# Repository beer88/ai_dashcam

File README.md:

# AI Dashcam System

An AI-powered Dashcam system built using Raspberry Pi that provides real-time video recording, intelligent event detection, and vehicle monitoring. The system integrates hardware and software components to enhance driving safety and provide smart surveillance capabilities.

## Features

- Real-time video recording using Raspberry Pi Camera
- AI-based object detection
- Automatic event recording
- GPS tracking support
- GSM/4G connectivity for remote monitoring
- Data storage on SD card
- Easy integration with vehicle systems

## Hardware Components

- Raspberry Pi 4
- Raspberry Pi Camera Module
- GPS Module
- GSM/4G Module
- Micro SD Card
- Power Supply Module
- Vehicle Mount

## Software Requirements

- Python 3
- OpenCV
- TensorFlow / PyTorch
- Raspberry Pi OS
- Git

## Project Structure

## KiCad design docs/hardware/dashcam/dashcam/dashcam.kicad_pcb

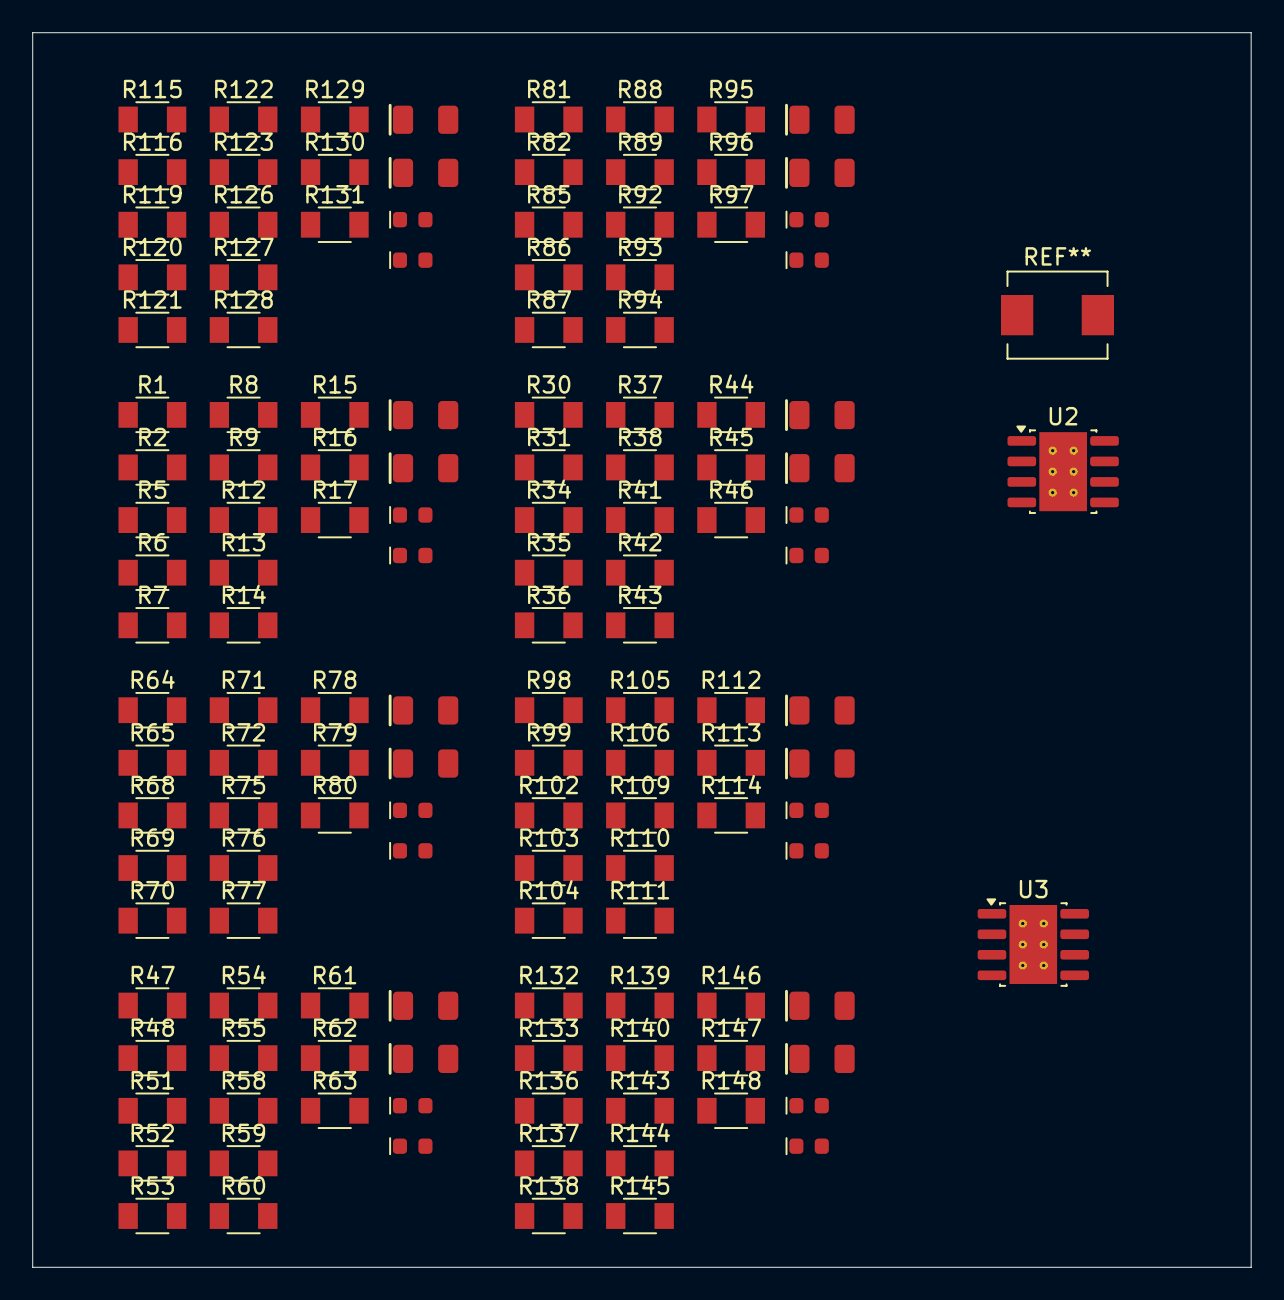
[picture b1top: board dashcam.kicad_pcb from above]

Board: 2 copper layers, 75.5 x 76.5 mm, 138 parts (0 on the bottom side), 69 nets, no tracks yet.

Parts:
D4, D5, D20, D21, D31, D32, D42, D43, D53, D54, D64, D65, D75, D76, D86, D87: LED; LED_0603_1608Metric
D6, D22, D33, D44, D55, D66, D77, D88: Green; LED_1206_3216Metric_Green
D7, D23, D34, D45, D56, D67, D78, D89: Blue; LED_1206_3216Metric_Blue
R1, R2, R6, R8, R9, R30, R31, R35, R37, R38, R47, R48, R52, R54, R55, R64, R65, R69, R71, R72, R81, R82, R86, R88, R89, R98, R99, R103, R105, R106, R115, R116, R120, R122, R123, R132, R133, R137, R139, R140: 33Ω; R_1206
R5, R7, R12, R17, R34, R36, R41, R46, R51, R53, R58, R63, R68, R70, R75, R80, R85, R87, R92, R97, R102, R104, R109, R114, R119, R121, R126, R131, R136, R138, R143, R148: 10k; R_1206
R13, R15, R42, R44, R59, R61, R76, R78, R93, R95, R110, R112, R127, R129, R144, R146: 330Ω; R_1206
R14, R16, R43, R45, R60, R62, R77, R79, R94, R96, R111, R113, R128, R130, R145, R147: 1k; R_1206
U2, U3: TPS54560BDDA; Texas_R-PDSO-G8_EP2.95x4.9mm_Mask2.4x3.1mm_ThermalVias

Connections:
/00_System_Overview.kicad_sch/3V3: R5.1, R12.1, R17.1
/00_System_Overview.kicad_sch/GND: D4.2 (A), D5.2 (A), D6.2 (A), D7.2 (A)
/00_System_Overview.kicad_sch/MOSI: R6.2, R7.2
/00_System_Overview.kicad_sch/SD_CMD: R6.1, R7.1
/01_Power_Supply.kicad_sch/+4V_LTE: U2.5 (FB), U3.5 (FB)
/01_Power_Supply.kicad_sch/+12V_FILTERED: U2.2 (VIN), U3.2 (VIN)
/01_Power_Supply.kicad_sch/GND: U2.7 (GND), U2.9 (GND)
/01_Power_Supply.kicad_sch/SW: U2.8 (SW), U3.8 (SW)
/02_Raspberry_Pi_Core.kicad_sch/3V3: R34.1, R41.1, R46.1
/02_Raspberry_Pi_Core.kicad_sch/GND: D20.2 (A), D21.2 (A), D22.2 (A), D23.2 (A)
/02_Raspberry_Pi_Core.kicad_sch/MOSI: R35.2, R36.2
/02_Raspberry_Pi_Core.kicad_sch/SD_CMD: R35.1, R36.1
/03_CSI_Camera_Interface.kicad_sch/3V3: R51.1, R58.1, R63.1
/03_CSI_Camera_Interface.kicad_sch/GND: D31.2 (A), D32.2 (A), D33.2 (A), D34.2 (A)
/03_CSI_Camera_Interface.kicad_sch/MOSI: R52.2, R53.2
/03_CSI_Camera_Interface.kicad_sch/SD_CMD: R52.1, R53.1
/04_LTE_Module.kicad_sch/3V3: R68.1, R75.1, R80.1
/04_LTE_Module.kicad_sch/GND: D42.2 (A), D43.2 (A), D44.2 (A), D45.2 (A)
/04_LTE_Module.kicad_sch/MOSI: R69.2, R70.2
/04_LTE_Module.kicad_sch/SD_CMD: R69.1, R70.1
/05_Audio_Microphone.kicad_sch/3V3: R85.1, R92.1, R97.1
/05_Audio_Microphone.kicad_sch/GND: D53.2 (A), D54.2 (A), D55.2 (A), D56.2 (A)
/05_Audio_Microphone.kicad_sch/MOSI: R86.2, R87.2
/05_Audio_Microphone.kicad_sch/SD_CMD: R86.1, R87.1
/06_Storage.kicad_sch/3V3: R102.1, R109.1, R114.1
/06_Storage.kicad_sch/GND: D64.2 (A), D65.2 (A), D66.2 (A), D67.2 (A)
/06_Storage.kicad_sch/MOSI: R103.2, R104.2
/06_Storage.kicad_sch/SD_CMD: R103.1, R104.1
/07_User_Interface.kicad_sch/3V3: R119.1, R126.1, R131.1
/07_User_Interface.kicad_sch/GND: D75.2 (A), D76.2 (A), D77.2 (A), D78.2 (A)
/07_User_Interface.kicad_sch/MOSI: R120.2, R121.2
/07_User_Interface.kicad_sch/SD_CMD: R120.1, R121.1
/08_External_Connectors.kicad_sch/3V3: R136.1, R143.1, R148.1
/08_External_Connectors.kicad_sch/GND: D86.2 (A), D87.2 (A), D88.2 (A), D89.2 (A)
/08_External_Connectors.kicad_sch/MOSI: R137.2, R138.2
/08_External_Connectors.kicad_sch/SD_CMD: R137.1, R138.1
unnamed: U3.7 (GND), U3.9 (GND)
unnamed: D4.1 (K), R15.2
unnamed: D5.1 (K), R16.2
unnamed: D6.1 (K), R13.2
unnamed: D7.1 (K), R14.2
unnamed: D20.1 (K), R44.2
unnamed: D21.1 (K), R45.2
unnamed: D22.1 (K), R42.2
unnamed: D23.1 (K), R43.2
unnamed: D31.1 (K), R61.2
unnamed: D32.1 (K), R62.2
unnamed: D33.1 (K), R59.2
unnamed: D34.1 (K), R60.2
unnamed: D42.1 (K), R78.2
unnamed: D43.1 (K), R79.2
unnamed: D44.1 (K), R76.2
unnamed: D45.1 (K), R77.2
unnamed: D53.1 (K), R95.2
unnamed: D54.1 (K), R96.2
unnamed: D55.1 (K), R93.2
unnamed: D56.1 (K), R94.2
unnamed: D64.1 (K), R112.2
unnamed: D65.1 (K), R113.2
unnamed: D66.1 (K), R110.2
unnamed: D67.1 (K), R111.2
unnamed: D75.1 (K), R129.2
unnamed: D76.1 (K), R130.2
unnamed: D77.1 (K), R127.2
unnamed: D78.1 (K), R128.2
unnamed: D86.1 (K), R146.2
unnamed: D87.1 (K), R147.2
unnamed: D88.1 (K), R144.2
unnamed: D89.1 (K), R145.2

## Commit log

2026-03-04 Revise README to enhance project details and structure
    Expanded project description and added features, hardware components, and software requirements sections.
2026-03-04 Add .gitignore file for Python and IDE files
2026-03-04 Add initial dependencies to requirements.txt
2026-03-04 Create CONTRIBUTING.md with contribution steps
    Added contributing guidelines for project collaboration.
2026-03-04 Add Code of Conduct for project contributors
2026-03-04 Add project structure documentation
2026-03-04 Create Code of Conduct
